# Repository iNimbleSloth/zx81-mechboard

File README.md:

# ZX81-mechboard
Mechanical keyboard for the ZX81 plus 38 (https://github.com/mahjongg2/ZX81plus38)

This keyboard is designed to use Cherry MX or Gateron switches. <br>
The keyboard is open source, please feel free to modiy it but always link back to this repository.<br>

Watch my video series that features this keyboard on [YouTube](https://www.youtube.com/watch?v=6a8wxj9vJjU&list=PLx7VS_ZJdQyVQSyDkv-Idc9wqWm_9QVhM)<br><br>
KiCAD files_v1.1 - Schematic and PCB layout files for KiCAD<br>
keycaps layout - Keycaps design layout for Adobe Illustrator. Note that if useing wasdkeyboards, then you nned to use the expanded file.<br><br>
Available on [PCBWay Shared Projects](https://www.pcbway.com/project/shareproject/ZX81_Mechanical_Keyboard_68c46a1b.html)<br>

<br><br>
Keycaps printed by wasdkeyboards.com

<br>
Keycaps with sticky labels<br>

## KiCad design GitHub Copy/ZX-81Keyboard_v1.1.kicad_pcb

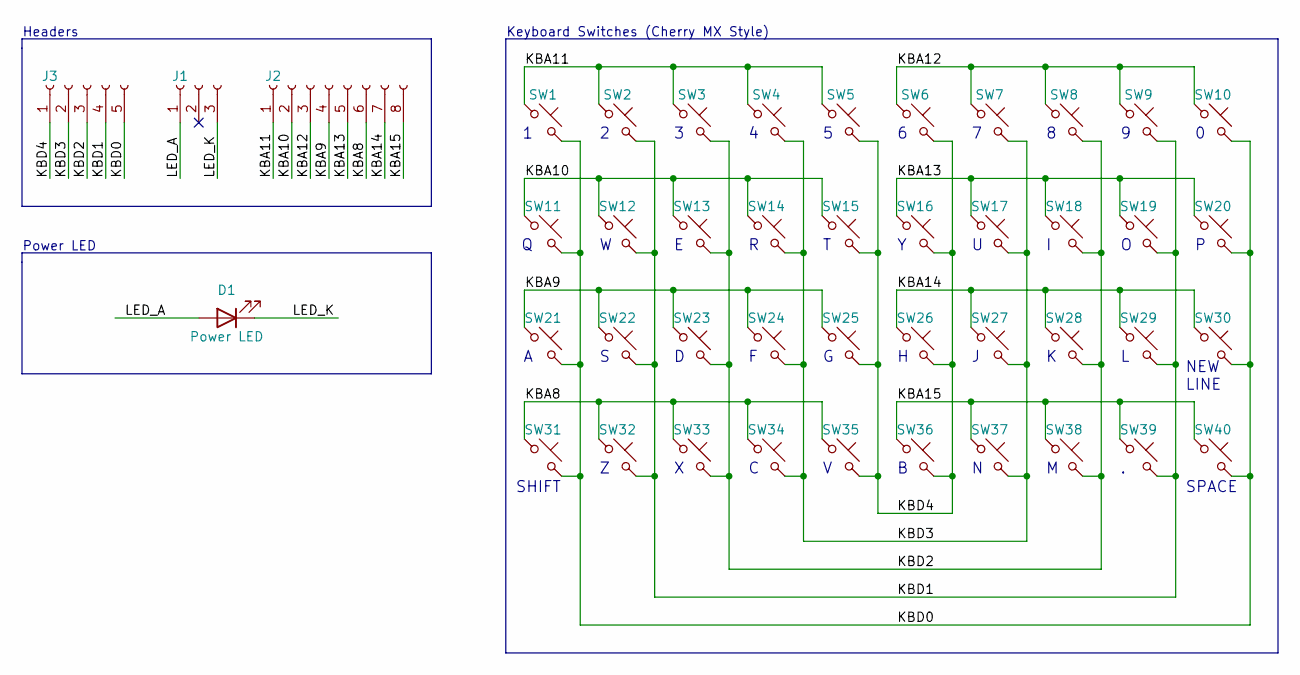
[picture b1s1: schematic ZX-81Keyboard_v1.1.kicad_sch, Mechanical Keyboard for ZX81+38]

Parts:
D1: Power LED; LED_1206_3216Metric_Pad1.42x1.75mm_HandSolder
J1: Conn_01x03_Female; PinSocket_1x03_P2.54mm_Vertical
J2: Conn_01x08_Female; PinSocket_1x08_P2.54mm_Vertical
J3: Conn_01x05_Female; PinSocket_1x05_P2.54mm_Vertical
SW1: 1; SW_Cherry_MX_1.00u_PCB
SW2: 2; SW_Cherry_MX_1.00u_PCB
SW3: 3; SW_Cherry_MX_1.00u_PCB
SW4: 4; SW_Cherry_MX_1.00u_PCB
SW5: 5; SW_Cherry_MX_1.00u_PCB
SW6: 6; SW_Cherry_MX_1.00u_PCB
SW7: 7; SW_Cherry_MX_1.00u_PCB
SW8: 8; SW_Cherry_MX_1.00u_PCB
SW9: 9; SW_Cherry_MX_1.00u_PCB
SW10: 0; SW_Cherry_MX_1.00u_PCB
SW11: Q; SW_Cherry_MX_1.00u_PCB
SW12: W; SW_Cherry_MX_1.00u_PCB
SW13: E; SW_Cherry_MX_1.00u_PCB
SW14: R; SW_Cherry_MX_1.00u_PCB
SW15: T; SW_Cherry_MX_1.00u_PCB
SW16: Y; SW_Cherry_MX_1.00u_PCB
SW17: U; SW_Cherry_MX_1.00u_PCB
SW18: I; SW_Cherry_MX_1.00u_PCB
SW19: O; SW_Cherry_MX_1.00u_PCB
SW20: P; SW_Cherry_MX_1.00u_PCB
SW21: A; SW_Cherry_MX_1.00u_PCB
SW22: S; SW_Cherry_MX_1.00u_PCB
SW23: D; SW_Cherry_MX_1.00u_PCB
SW24: F; SW_Cherry_MX_1.00u_PCB
SW25: G; SW_Cherry_MX_1.00u_PCB
SW26: H; SW_Cherry_MX_1.00u_PCB
SW27: J; SW_Cherry_MX_1.00u_PCB
SW28: K; SW_Cherry_MX_1.00u_PCB
SW29: L; SW_Cherry_MX_1.00u_PCB
SW30: NEW LINE; SW_Cherry_MX_1.00u_PCB
SW31: SHIFT; SW_Cherry_MX_1.00u_PCB
SW32: Z; SW_Cherry_MX_1.00u_PCB
SW33: X; SW_Cherry_MX_1.00u_PCB
SW34: C; SW_Cherry_MX_1.00u_PCB
SW35: V; SW_Cherry_MX_1.00u_PCB
SW36: B; SW_Cherry_MX_1.00u_PCB
SW37: N; SW_Cherry_MX_1.00u_PCB
SW38: M; SW_Cherry_MX_1.00u_PCB
SW39: .; SW_Cherry_MX_1.00u_PCB
SW40: SPACE; SW_Cherry_MX_1.00u_PCB

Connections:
/KBA8: J2.6, SW31.1, SW32.1, SW33.1, SW34.1, SW35.1
/KBA9: J2.4, SW21.1, SW22.1, SW23.1, SW24.1, SW25.1
/KBA10: J2.2, SW11.1, SW12.1, SW13.1, SW14.1, SW15.1
/KBA11: J2.1, SW1.1, SW2.1, SW3.1, SW4.1, SW5.1
/KBA12: J2.3, SW6.1, SW7.1, SW8.1, SW9.1, SW10.1
/KBA13: J2.5, SW16.1, SW17.1, SW18.1, SW19.1, SW20.1
/KBA14: J2.7, SW26.1, SW27.1, SW28.1, SW29.1, SW30.1
/KBA15: J2.8, SW36.1, SW37.1, SW38.1, SW39.1, SW40.1
/KBD0: J3.5, SW1.2, SW10.2, SW11.2, SW20.2, SW21.2, SW30.2, SW31.2, SW40.2
/KBD1: J3.4, SW2.2, SW9.2, SW12.2, SW19.2, SW22.2, SW29.2, SW32.2, SW39.2
/KBD2: J3.3, SW3.2, SW8.2, SW13.2, SW18.2, SW23.2, SW28.2, SW33.2, SW38.2
/KBD3: J3.2, SW4.2, SW7.2, SW14.2, SW17.2, SW24.2, SW27.2, SW34.2, SW37.2
/KBD4: J3.1, SW5.2, SW6.2, SW15.2, SW16.2, SW25.2, SW26.2, SW35.2, SW36.2
/LED_A: D1.2 (A), J1.1
/LED_K: D1.1 (K), J1.3

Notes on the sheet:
SPACE
Headers
SHIFT
Power LED
NEW LINE
Keyboard Switches (Cherry MX Style)

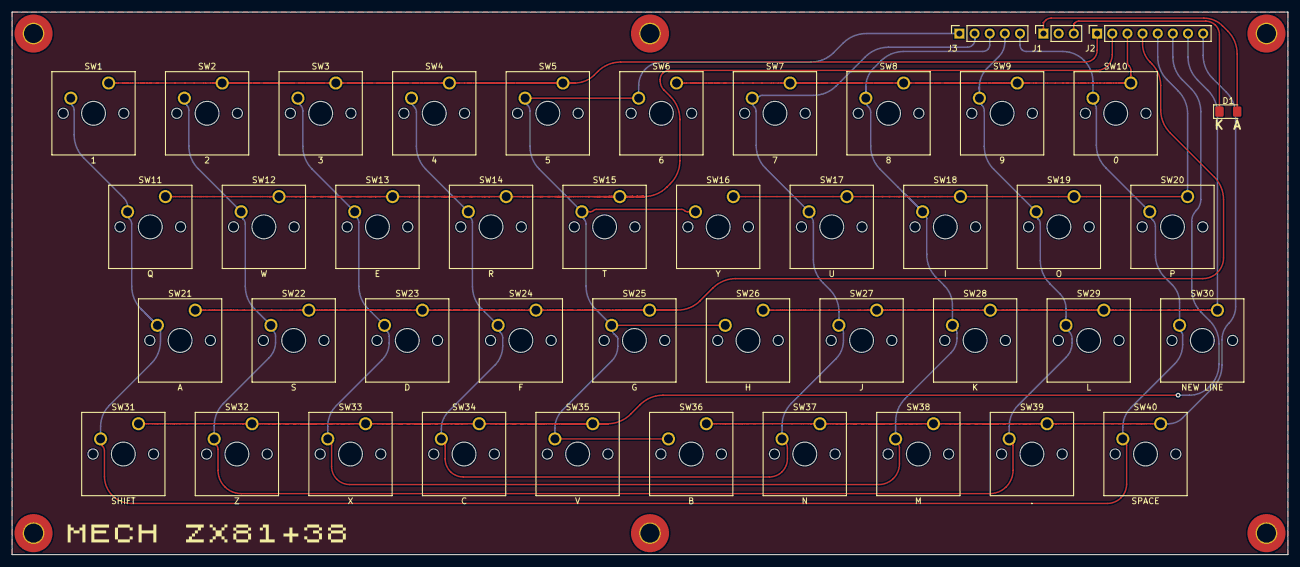
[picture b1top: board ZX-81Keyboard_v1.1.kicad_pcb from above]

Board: 2 copper layers, 214.0 x 91.0 mm, 44 parts (0 on the bottom side), 15 nets.

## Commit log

2023-12-11 Create ZX81+38 Case
2023-12-11 Create 1
